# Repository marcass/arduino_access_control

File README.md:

# arduino_access_control
* Use arduino to control access to electrically actuated devices

## Components
* Electronically actuated device (garage door/door/or anything you want to access)
* WiFi in range
* Arduino as node/client (communicates to network using ESP8266 and [WIFIESP](https://github.com/bportaluri/WiFiEsp) arduino lib)
* Arduino runs this [MQTT lib](https://github.com/256dpi/arduino-mqtt)
* A master/server that runs mosquitto and a webserver

## How it works
1. Pincode gets sent to topic for door requests (either by pinpad, mqttclient, web interface, rfid device etc)
2. Pincode checked against database of allowed users
3. Response is sent to the node (allow or deny)
4. Relay is actuated and DB is updated

## User managment
Users added, modified and deleted via webpage in webserver (https://<servername/URL>)

## Maintenace
### Initial setup
* Update doorsetup.py to reflect doors you want to control
* run `python views.py <admin username> <admin password>` You get to choose what they are!
* Stop script then run via systemd (or whaterever process manager you use)
* Populate db via web interface (login usng credentials supplied above above)

### ssl certs
Letsencrypt cert needs to be renewed periodically:
1. Open port 80 on router to webserver (need to enable ipv6 for fritzbox to allow this then disable as ISP falls apart with IPv6 used)
2. run `sudo certbot renew`
3. Disable access via port 80

## Troubleshooting
### My uwsgi won't work (upstream timeout errors in /var/log/nginx/error.log)
* `# systemclt stop door`
* running (from python dir) $ uwsgi --ini uwsgi.py
* Ctrl+C that process after testing api is delivering
* `# systemctl start door`
This seems to work

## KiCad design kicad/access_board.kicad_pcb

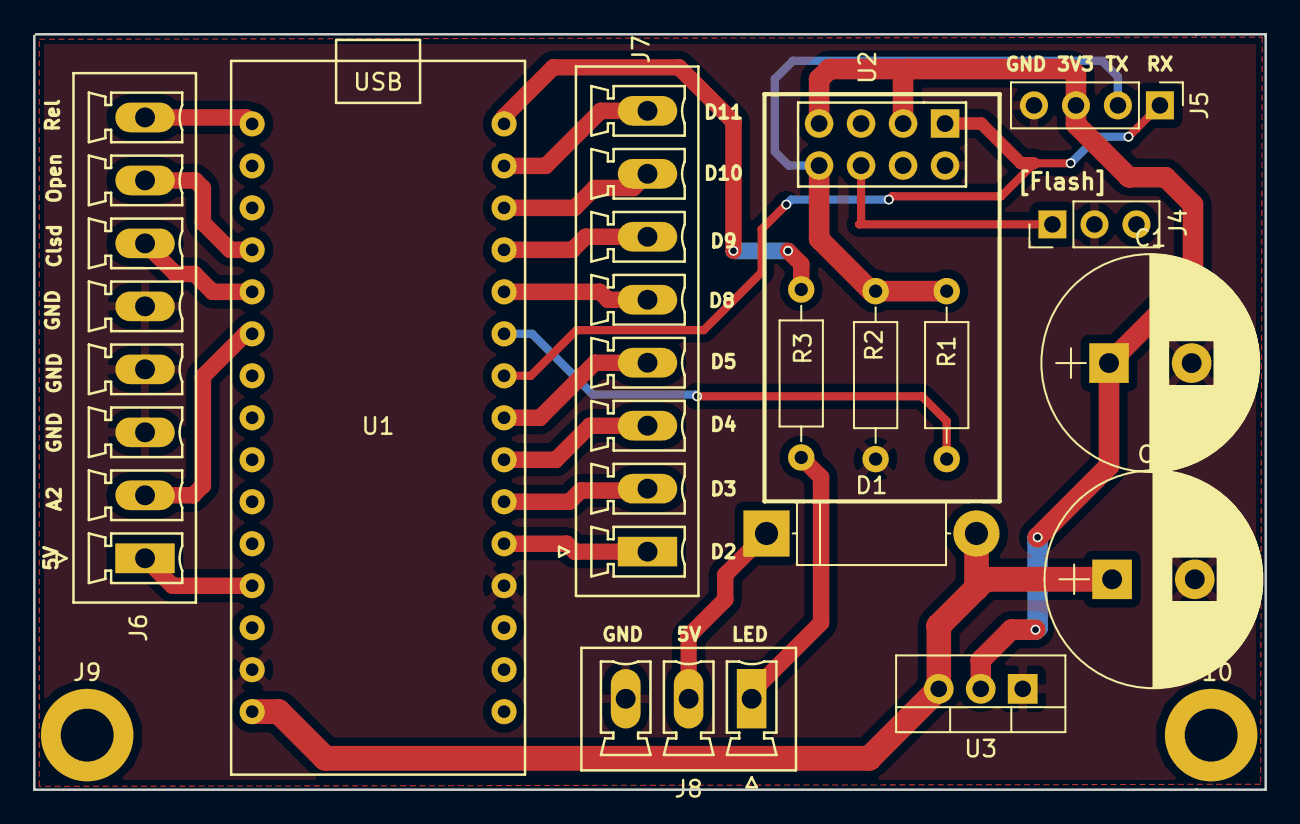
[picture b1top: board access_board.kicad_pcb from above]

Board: 2 copper layers, 74.5 x 45.7 mm, 16 parts (0 on the bottom side), 23 nets.

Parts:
C1, C2: 1000uF; CP_Radial_D13.0mm_P5.00mm
D1: D; D_5W_P12.70mm_Horizontal
J4: CONN_01X03; Pin_Header_Straight_1x03_Pitch2.54mm
J5: CONN_01X04; Pin_Header_Straight_1x04_Pitch2.54mm
J6, J7: CONN_01X08; PhoenixContact_MCV-G_08x3.81mm_Vertical
J8: CONN_01X03; PhoenixContact_MCV-G_03x3.81mm_Vertical
J9, J10: CONN_01X01; MountingHole_3.2mm_M3_DIN965_Pad
R1: 1k; R_Axial_DIN0207_L6.3mm_D2.5mm_P10.16mm_Horizontal
R2: 2.2k; R_Axial_DIN0207_L6.3mm_D2.5mm_P10.16mm_Horizontal
R3: 470; R_Axial_DIN0207_L6.3mm_D2.5mm_P10.16mm_Horizontal
U1: arduino_nano; ArduinoNano
U2: ESP-01v090; ESP-01
U3: LD1117S33TR; TO-220_Vertical

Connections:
2: J7.1, U1.20
3: J7.2, U1.21
4: J7.3, U1.22
5: J7.4, U1.23
8: J7.5, U1.26
9: J7.6, U1.27
10: J7.7, U1.28
11: J7.8, U1.29
+3V3: C1.1, J5.3, U2.3, U2.7, U3.2
+5V: J6.1, U1.12
A2: J6.2, U1.6
Closed: J6.6, U1.5
GND: C1.2, C2.2, J4.2, J5.4, J6.3, J6.4, J6.5, J8.3, R2.1, U1.14, U1.19, U2.2, U3.1
GPIO0: J4.1, U2.6
LED: R3.2, U1.30
unnamed: D1.1, J8.2
unnamed: J8.1, R3.1
unnamed: R1.1, U1.25
OPEN: J6.7, U1.4
RX: J5.1, U1.24, U2.1
TX: J5.2, R1.2, R2.2, U2.8
VIN: C2.1, D1.2, U1.15, U3.3
relay: J6.8, U1.1

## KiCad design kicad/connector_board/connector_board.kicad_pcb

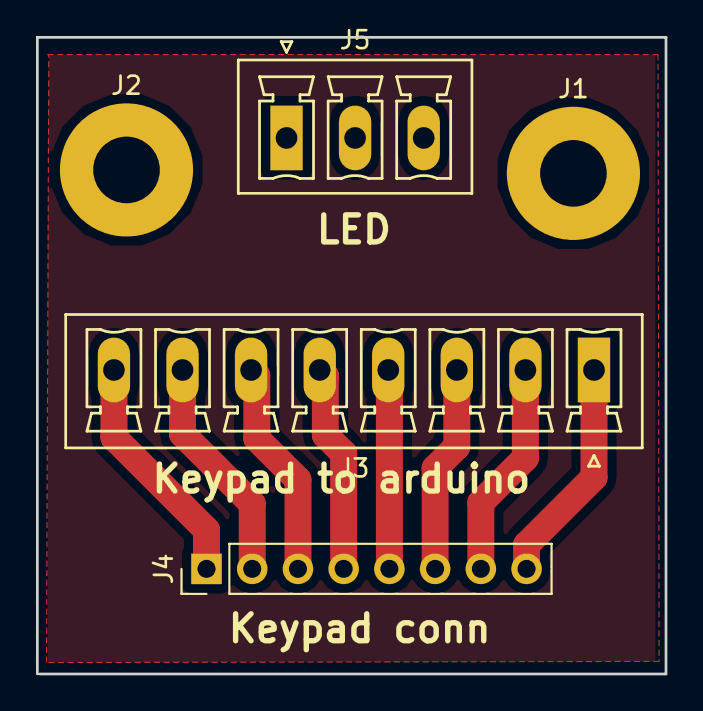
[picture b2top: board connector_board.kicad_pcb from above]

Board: 2 copper layers, 34.9 x 35.4 mm, 5 parts (0 on the bottom side), 8 nets.

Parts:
J1, J2: CONN_01X01; MountingHole_3.7mm_Pad
J3: CONN_01X08; PhoenixContact_MCV-G_08x3.81mm_Vertical
J4: CONN_01X08; Pin_Header_Straight_1x08_Pitch2.54mm
J5: CONN_01X03; PhoenixContact_MCV-G_03x3.81mm_Vertical

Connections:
unnamed: J3.1, J4.8
unnamed: J3.2, J4.7
unnamed: J3.3, J4.6
unnamed: J3.4, J4.5
unnamed: J3.5, J4.4
unnamed: J3.6, J4.3
unnamed: J3.7, J4.2
unnamed: J3.8, J4.1

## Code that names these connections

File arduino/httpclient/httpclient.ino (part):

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
#define RED_LED 10
#define GREEN_LED 11
#define CLOSED A0
#define OPEN A1
#define RELAY 12
#define LEDPIN 13
int door_state;
int open_reed;
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  digitalWrite(RED_LED, LOW);
  pinMode(GREEN_LED, OUTPUT);
  digitalWrite(GREEN_LED, LOW);
  pinMode(OPEN, INPUT_PULLUP);
  pinMode(CLOSED, INPUT_PULLUP);
  pinMode(RELAY, OUTPUT); 
  pinMode(LEDPIN, OUTPUT);
  digitalWrite(RELAY, HIGH);
  digitalWrite(LEDPIN, LOW);
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  const size_t bufferSize = JSON_OBJECT_SIZE(1) + 20;
  // Allocate a temporary memory pool
  DynamicJsonBuffer jsonBuffer(bufferSize);
  //const char* json = "{\"open\":\"true\"}";
  JsonObject& root = jsonBuffer.parseObject(client);
  
  if (!root.success()) {
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
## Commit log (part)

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2017-09-06 initial population of files that need to be configured
2017-09-06 keypad stuff
2017-09-07 updating sketch
2017-09-07 updated arduino sketch and added max's flask server example
2017-09-08 building on keyserver
2017-09-08 backend stuff
2017-09-08 sql for users created and tested
2017-09-08 successful get from db
2017-09-09 trimmed down database stuff
2017-09-09 got logs
2017-09-10 working with multiple doors
2017-09-10 best add this
2017-09-10 vue stuff and api trimming (or expansion)
2017-09-11 making flask play nice with sql
2017-09-11 FUCK!
2017-09-11 morepolishing api
2017-09-12 fiddling with frontend
2017-09-12 more frontend
2017-09-12 updated more frontend
2017-09-13 date parsing
2017-09-13 time sorted but not updating in users
2017-09-14 updateing frontend
2017-09-14 more cfrontend again
2017-09-14 moving elements around
2017-09-14 fully functional api, now needs beutifying
2017-09-15 started pcb dev
2017-09-15 addedd forked esp lib
2017-09-18 schematic update
2017-09-20 refactoring sketch
2017-09-21 arduino tests
2017-09-21 updated sytax for production build of frontend
2017-09-25 got ssl with websockets working
2017-09-25 localised for server
2017-09-25 adding sockets functionality - tested and working
2017-09-25 low memmory on arduino in production and connection failing for some reason
2017-09-25 sketch fluffing
2017-09-26 json for door response
2017-09-26 sketch mods. High mem use
2017-09-26 discarded ArduinoJSON due to memory footprint
2017-09-26 modifying string for response
2017-09-26 sketches updating
2017-09-26 keyserver update for json
2017-09-26 finally it works (with freq disconnects for mwebsocket)
2017-09-26 disconnecting after each websocket call
2017-10-02 Start mqtt
2017-10-04 arduino mqtt done
2017-10-04 setup python side of mqtt
2017-10-05 refining for broker connection
2017-10-05 testing mqtt and python
2017-10-05 sketch refinement
2017-10-05 working mqtt now
2017-10-06 changed qos in mqtt
2017-10-06 updated mqtt for qos adn got it working
2017-10-06 tested and working arduino script
2017-10-06 fixed typo in topics
2017-10-06 door states added
2017-10-07 added door status to python
2017-10-07 door status problems
2017-10-07 status progress
2017-10-08 fixed door status updates
2017-10-08 fixed status updates
2017-10-08 working over ssl for requrests
2017-10-09 validating mqtt users
2017-10-09 concantenated auth of keys adn start jwt stuff
2017-10-10 updated kicad schematic
2017-10-11 pcb layout
2017-10-11 more pcb stuff
2017-10-12 added neopixel and continued with pdb
2017-10-12 updated pcb
2017-10-14 keyserver fluffing
2017-10-14 updated qos of subscription to 2
2017-10-14 changed qos level to 0 due to problems with arduino mqtt lib at qos 2
2017-10-15 updated caps and checked diode size on board, started sketch mod for leds
2017-10-16 added connector board as a different kicad file
2017-10-16 setting up sketch for pixels and updated connector board
2017-10-17 leds coded for sketch, now need to test
2017-10-17 python reorg
2017-10-19 reshuffle for jwt
2017-10-25 starting vue2 auth via jwt
2017-10-26 vue auth stuff
2017-10-26 linting has started
2017-10-27 grinding on with auth in vuejs2
2017-10-27 starting again...
2017-10-27 gettng tokens, now need to do something with them
2017-10-29 got jwt working in messy fashion
2017-10-29 changed routes to suit vue-auth
2017-10-29 working with auth in rudimentary way
2017-10-29 polishing api
2017-10-29 adding jwt_required to routes
2017-10-29 updated keyserver for door status updates
2017-10-29 dumped junk in vuejs
2017-10-29 getting rid of vuejs extras (again)
2017-10-31 user verification for sql db
2017-10-31 testing user in db
2017-10-31 syncing flask server
2017-10-31 updating server for debugging
2017-10-31 fiddling
2017-10-31 user permissions on pages: not working
2017-10-31 keyserver now working with hashed and salted pw's
2017-11-01 synicng server
2017-11-01 can't get roles working
2017-11-01 page update
2017-11-01 mods to sql ret_dict
2017-11-01 fiddling with roles, making progress
2017-11-01 got roles working
2017-11-01 added user specific route
2017-11-02 sorting delete in db
2017-11-03 page refinement
2017-11-03 page fiddling
2017-11-03 page rendering
2017-11-03 entered diode value
2017-11-05 final sketch working
2017-11-05 turd polishing
2017-11-05 sorted status error
2017-11-05 user verification for password change
2017-11-05 password changes and status verification
2017-11-06 getting status log working, among other things
2017-11-07 logging of door stuff...
2017-11-07 api polishing
2017-11-07 handling log
2017-11-07 wokring response, empty data
2017-11-07 got logging working
2017-11-07 removed most of debugging prints from api
2017-11-07 set retained flag for status messages
2017-11-07 fucking around with time formats on status log
2017-11-08 more datetime shit
2017-11-08 cnaged displayed date object as can't get js to handle timezone reliably
2017-11-08 fucking dates
2017-11-08 got dates working for one door at a time in status page
2017-11-08 changing displays on log pages
2017-11-08 removed debugging prints from api
2017-11-09 got times for new user sorted
2017-11-09 tidied date handling for update
2017-11-09 updated date formatting for processing in sql.py
2017-11-10 making files more illegible by the day
2017-11-10 trying to display statyus and getting into either a loop or trying to disply a getter
2017-11-13 getter hell
2017-11-14 sorted door status problem (not prviding a list duh)
2017-11-14 made api provide a list to iterate through for door status
2017-12-04 file reshuffle
2017-12-04 got leds working - needed timer to cause delay so lib could catch up
2018-02-11 Update command to set baud rate to esp module for software serial
2018-02-20 Added other config bits
2018-02-23 updated for bottom
2018-02-26 added flashing file and updated serial instructions
2018-02-27 fixed message received problem via mqtt
2018-03-01 app polishing for responsivness and one look status
2018-03-02 updates to pages
2018-03-02 trying to get navbar to behave
2018-03-02 fucking aroudn with menus. tey all suck and I should write my own
2018-03-05 still menuing
2018-03-06 menus links working when router in historyu mode
2018-03-06 fixed broken nav file
2018-03-06 finally sorted menu
2018-03-07 sent for production
2018-03-28 got menu working on mobile and removed horzontal scroll issue
2018-05-02 trying to resolve menu display
2018-05-09 getting mounted sorted slowly
2018-05-09 have working created hook, but still needs polishin
2018-05-10 altered routes and login detail. still testing
2018-06-11 tidy up
2018-06-12 tidying up logins
2018-06-13 cannot redirect to home page
2018-06-14 debugging login
2018-06-14 login tuff
2018-06-14 added uwsgi and tidied CSS
2018-06-14 sorted error handling for ghost in teh post
2018-06-14 satrted deploying via uwsgi
2018-06-14 can't get post login to redirect to right page
2018-06-15 working now (beaerer was pointing to wrong file in main.js)
2018-06-16 hmmm, not using requests so not sure why door failing at pinpad
2018-06-16 uwsgi problem wiht mqtt.py
2018-06-16 debugging uwsgi
2018-06-16 will see how this goes
2018-06-16 needed threads
2018-06-16 removed debugging prints
2018-06-17 sorting out secret for jwt, uwsgi rationalisation
2018-06-17 logout method/page established
2018-06-17 Logout route, failing with refresh token
2018-06-17 started jwt auth for python modules so they can access routes
2018-06-17 making python authenticate to protect db
2018-06-17 making python authenticate to protect db, and tidying
2018-06-17 not enough debug
2018-06-18 getting jwt working for helper apps
2018-06-18 got auth working, not fiddling with refresh yet
2018-06-18 reverting to direct database calls as systemd not handling processes for jwt auth of python modules
2018-06-19 making log more sensible
2018-06-19 keeping up to date
2018-06-19 ping
2018-06-19 pong
2018-06-19 tidying up
2018-06-19 updateing
2018-06-19 getting front end logging sorted
2018-06-19 tidying up debugs
2018-06-19 stop filling db!
2018-06-19 not spamming db now
2018-06-19 getting rid of logging
2018-06-20 can delete a door now
2018-06-20 working on tidying doors (german)
2018-06-21 pruning
2018-06-22 tidying up messages
2018-06-22 updated backend to smoooth errors
2018-06-22 updated front end
2018-06-22 more front end tidying
2018-06-22 so many responses..
2018-06-22 ordering results
2018-06-22 finished status log
2018-06-22 getting auth on keycode change sorted
2018-06-22 refineind front end
2018-06-22 spelling errors
2018-06-23 trying to get api calls from python working with jwt auth
2018-07-22 combined boiler and door stuff
2018-07-22 plotly developing along
2018-07-22 plotly stuff
2018-07-22 still fiddling multiple plots
2018-07-22 fomratting boiler page
2018-07-22 refining input for boiler
2018-07-23 front end stuff
2018-07-23 fiddling data
2018-07-23 more front end
2018-07-23 customising graph
2018-07-23 getting graphing sorted
2018-07-23 readme update
2018-07-23 layouts
2018-07-23 fucking plotyly won't build for production
2018-07-24 trying to build plotly - failing
2018-07-26 started rp's
2018-07-26 setting up retention policies - need to setup continuous queries
2018-07-27 possible continuous queries?
2018-07-31 CQ working it seems - amazing!
2018-07-31 rendering graph is annoying
2018-07-31 getting compound queries sorted - single or double quotes? waht about both
2018-08-01 getting RP sorted for inflx
2018-08-01 finally gotr CQ working in influxdb (use UTC for time
2018-08-01 plotly plotting in UTC - not converting UTC timestamps
2018-08-01 plotting getting there
2018-08-02 multigraphing displaying lines, not having much luck with axes
2018-08-02 mapping dates to localtime
2018-08-02 dates working for plotly now
2018-08-03 updating for boiler state
2018-08-03 missed brackets
2018-08-03 ironing out wrinkles
2018-08-03 more wrinkles
2018-08-06 updated readmen and started on esp32 code
2018-08-06 forgot this bit
2018-08-06 ksketch shaping up. need to parse json to get token
2018-08-06 dinner time
2018-08-06 updated role validation in api
2018-08-06 fix typi
2018-08-07 got state displaying
2018-08-07 updated frontend
2018-08-07 arduinohttpclient won't work with esp32
2018-08-07 found detail on http client
2018-08-07 moved website to another repo
2018-08-08 starting to test client on esp32
2018-08-08 RP update for sensors db
2018-08-08 working route for a sensor tested with curl
2018-08-08 still not working for multiple header request
2018-08-08 getting data in from esp32
2018-08-08 non ssl arduino sketch working
2018-08-09 got tls working
2018-08-09 spilling data from database
2018-08-10 front end prep on api
2018-08-10 stuff
2018-08-10 data retreeival being updated
2018-08-10 sorting data retreival
2018-08-10 getting data out now
2018-08-11 data actually coming through now
2018-08-11 who knew returning values could be this hard?
2018-08-11 another schema rejig
2018-08-12 trying to get it to spit data for graphing
2018-08-12 refining data retreival
2018-08-13 getting data
2018-08-14 2 y-axes?
2018-08-14 mulitple axes
2018-08-14 parsing layouts
2018-08-14 polishing
2018-08-15 refactor
2018-08-16 getting it to loop foreever
2018-08-16 working split api
2018-08-22 changed route for api
2018-08-22 sorted the damn door problem with now api routes
2019-02-02 testing hcc temps on mosquitto
2019-02-02 feeding temps to influx now
2019-02-02 getting temps into influx, removed print lines
2019-02-04 esp32 LR tests
2019-02-26 rationalising applicaitons
2019-02-26 range testing lr connection on esp32
2019-07-15 altering code for esp. Up to checking state at startup
2019-07-15 compiles, now need to test
2019-07-16 uploads and works with mqtt sub/pub
2019-07-16 working prototype
2019-07-16 keypad problem
2019-07-17 working via mqtt
2019-07-17 updated systemd file for dirty fix
2019-07-17 fixed overly complex tests on door status
2019-07-21 made status message retained
2019-07-31 updated retain flags and LWT
2019-07-31 placed message for being online
2019-08-05 got status reporting sorted
2019-08-10 publishing status and updated LWT
2019-09-13 given up on arduino and esp8266
2019-09-13 bottom door movintg to esp32
2019-10-10 added oled screen for debugging
2019-10-10 updated pins
